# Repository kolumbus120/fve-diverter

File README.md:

# FVE diverter — solar surplus diverter for a Daikin heat-pump house (ESPHome + Home Assistant)

*[Slovenská verzia → README.sk.md](README.sk.md)*

An ESP32 (ESPHome) that sends **solar PV surplus into two electric heaters**: the domestic
hot water tank (3 kW element) and the underfloor heating water (~600 W element). Each heater is
driven by a TRIAC board controlled over I2C. Unlike a plain "keep the grid at 0 W" router, it
works with the **battery of a hybrid inverter (charging power and state of charge, SoC)** and with the **Daikin Altherma heat pump**. A set
of Home Assistant packages makes the slower decisions: when to turn the heat pump down because
the sun heats the house, when the heat pump must not heat the hot water because the sun will,
and a weekly heating plan with a custom Lovelace card.

It runs at home since 2026-11-15. The **PCB is designed and ordered but not built yet**
(see [PCB](#pcb--carrier-board) below).

*Main schematic: [SVG](docs/schematics/fve_schema_en.svg) · [PNG](docs/schematics/fve_schema_en.png) (Slovak original: [`fve_schema.svg`](docs/schematics/fve_schema.svg)).*

> Code comments and most of the docs in `docs/` are in **Slovak**. Entity names in Home Assistant
> are Slovak too (e.g. *TUV* = domestic hot water, *podlaha* = underfloor heating,
> *čerpadlo* = pump, *stykač* = contactor, *prebytok* = surplus, *okno FVE* = PV window).

## What it does

**ESP32 firmware** ([`esphome/fve-diverter.yaml`](esphome/fve-diverter.yaml)) — works without
Home Assistant too:

- **Measurement:** a Shelly 3EM-63 Gen3 at the grid connection is read directly by the ESP every
  2 s (local HTTP RPC). Battery power and SoC of the Solax hybrid inverter come from the Solax
  Cloud API through Home Assistant (about every 4 min).
- **How the surplus is split:** the floor first (0–600 W), then hot water and battery ¾ : ¼. The
  battery always keeps a 300 W reserve. At SoC ≥ 97 % everything goes to the hot water.
  - From the Shelly reading: when power is drawn from the grid, the heaters are cut quickly; when
    power flows out to the grid, they get more.
  - Each new Solax reading moves the heaters toward the target, taking into account what the
    heaters drew at the time of that reading.
- **Battery-aware (SoC):** unlike grid-only routers, it knows how much the battery is charging
  and its state of charge.
  - The battery gets its share first (300 W reserve, ¼ of the surplus above the floor element;
    the share is adjustable).
  - Once the battery counts as full (SoC ≥ 97 %, adjustable), the whole surplus goes to the hot
    water.
  - A weak Solcast forecast for tomorrow can raise the inverter's minimum SoC as a backup reserve
    (waits for a local Solax dongle).
- **Fail-safe:** no Shelly data for more than 15 s → heaters at 0 W. If Solax or HA is
  unavailable, an emergency Shelly-only mode heats only from the visible export and keeps about
  300 W of it.
- **TRIAC + contactors:** an isolation contactor in front of each TRIAC and a bypass contactor
  that takes over at ≥ 97 % power and opens again at ≤ 95 %. The TRIAC is held at 100 % before
  the bypass closes, so the contacts don't arc. At most one relay switches per 5 s cycle.
- **Phase-angle control** through DimmerLink: LINEAR curve plus a power → level table measured
  with the Shelly (error ≤ 1.5 %).
- **PV window from sunrise/sunset:** the window runs from sunrise + 2 h to sunset − 2 h. It is
  computed on the ESP with the ESPHome `sun:` component, and both offsets are adjustable.
  - Inside the window, the first surplus of at least 100 W lasting 5 min starts a **"sunny
    day"**. Only then do the contactors close, and they stay closed until the window ends.
  - On a cloudy day nothing switches at all.
  - The house sits in a valley: the history showed direct sun on the panels starts 2 h 40 min to
    3 h after sunrise and ends 2 h 15 min to 2 h 30 min before sunset.
- **Daikin integration via two 230 V AC opto inputs:**
  - Coil of the hydrobox **K3M** contactor (booster heater request) → the shared hot-water
    element runs at full power through the bypass, no matter what the PV is doing.
  - Floor pump request → floor circulation pump.
- **Limits:** hot water max 75 °C and floor water max 35 °C (adjustable, 2 °C hysteresis).
  - A failed DS18B20 (NaN) means no heating from PV.
  - TRIAC temperature is measured with an NTC.
- **Manual power** per heater, with a time limit (default 5 h) and a notification when it
  expires. After a reboot the ESP always returns to automatic mode.
- **Pumps:**
  - Floor pump: Auto (Daikin / PV heating) / always on / OFF.
  - Hot water circulation pump runs on tap use (flow meter), maintenance, during heating, and when
    the tank is hot while the sun shines.
  - Both pumps have a **hard OFF/ON mode for service** that overrides everything.
- **Fans:** 4-pin PWM cabinet fan with tachometer, following the TRIAC load; fans on the dimmer
  boards.
- **Energy counters (estimated):** hot water from PV, floor, and hot water via Daikin K3M.
  - The K3M energy is split into *from grid* / *from sun* using the Shelly: from grid = current
    grid import, at most the element power.
  - Daily and lifetime totals are kept on the ESP; weekly and monthly totals are utility meters
    in HA.
- **Diagnostics:** the reason for every regulation step, the measurement age, read-back from the
  DimmerLinks and more, all sent through HA to InfluxDB.

**Home Assistant** ([`home-assistant/`](home-assistant)):

- [`packages/fve_strategia.yaml`](home-assistant/packages/fve_strategia.yaml) — strategy:
  - **Daikin heating:** −10 °C water offset when it is a *sunny day* and the surplus is ≥ 700 W.
    At least 30 min between changes protects the compressor. On days without sun the heating plan
    runs untouched.
  - **Daikin hot water blocked so the sun can heat it:**
    - workdays 06:00–15:00;
    - days off: from the start of the PV window, released for the whole day if no sunny day
      starts within 60 min;
    - vacation: blocked all the time;
    - a manually started Daikin *performance* run always wins: it is never interrupted, and
      blocking is skipped for the rest of that day.
  - Tech M-9R zones +2 °C while the floor element runs at full power.
  - Hot water circulation during heating when somebody is at home.
  - Solcast forecast → Solax minimum SoC (waits for a local Solax dongle).
- [`packages/fve_energia.yaml`](home-assistant/packages/fve_energia.yaml) — weekly and monthly
  energy totals.
- **Heating plan:**
  - [`packages/daikin_plan_kurenia.yaml`](home-assistant/packages/daikin_plan_kurenia.yaml) — a
    weekly plan that switches between normal and setback by changing the water temperature offset
    on the Daikin.
  - It uses a week schedule plus a holiday schedule, Slovak public holidays (Workday + Holiday
    integrations), school holidays and vacation.
  - It produces one target-offset sensor; the sun-driven reduction from the strategy has priority.
  - Card [`www/plan-kurenia-card.js`](home-assistant/www/plan-kurenia-card.js) with dashboard
    [`dashboards/plan_kurenia.yaml`](home-assistant/dashboards/plan_kurenia.yaml): a weekly
    editor, today's plan, holiday list with on/off toggles, and a strip showing when the sun
    (PV strategy) and the low-tariff signal (HDO) were active.
- Dashboards: [`fve_diverter.yaml`](home-assistant/dashboards/fve_diverter.yaml) (operation),
  [`fve_diverter_test.yaml`](home-assistant/dashboards/fve_diverter_test.yaml) (service firmware).
- [`solax/`](home-assistant/solax) — Solax Cloud API v2 `command_line` sensor + script (until a
  local dongle is used).
- [`automations/`](home-assistant/automations) — notification when manual power expires.

**Grafana** ([`grafana/`](grafana)) — generator of a dashboard showing energy into the heaters
per day and power over time (InfluxDB v2 / Flux, data written by the HA InfluxDB integration).

## Hardware it was built and tested with

| Part | Used here | Notes |
|---|---|---|
| Controller | ESP32 DevKit 38-pin, ESPHome **2026.10.2** (Arduino framework) | pin map in [`esphome/README.md`](esphome/README.md) |
| TRIAC boards | 2× **RBDimmer** (rbdimmer.com) + 2× **DimmerLink** (I2C, 0x54 / 0x53) | modified DimmerLink component in [`esphome/components/dimmerlink`](esphome/components/dimmerlink) |
| Grid meter | **Shelly 3EM-63 Gen3** (`/rpc/EM.GetStatus`) | other Gen2+ Shelly EMs with the same RPC should work |
| Inverter | **Solax** hybrid with battery, Solax Cloud API v2 | without it: emergency Shelly-only mode |
| Heat pump | **Daikin Altherma 3** hydrobox EHBH08DA9W7 (K3M contactor = booster heater) | opto inputs on the K3M coil and the floor pump request |
| HA integrations | Home Assistant 2026.11, packages, `schedule`, Workday, Holiday; custom [`daikin_altherma`](https://github.com/tadasdanielius/daikin_altherma) (local LAN adapter) for the heating plan | Solcast, Tech controllers and ESPAltherma are optional |
| Other | DS18B20 ×3, 2-ch 230 V AC opto module, 2-ch relay modules, contactors, Hall flow meter, Mean Well MDR-20-5, 4-pin PWM fan | |

Adapt before use:
- the substitutions at the top of `fve-diverter.yaml`: `shelly_ip`, `latitude`, `longitude`;
- `secrets.yaml` (copy it from `secrets.yaml.example`);
- the element powers (calibrate with the Shelly);
- the DS18B20 addresses;
- the entity names in the HA packages (Daikin, Tech, Solax, notify).

## PCB — carrier board

[`pcb/`](pcb) — KiCad 9 project for a carrier board. The ESP32 and both DimmerLinks plug into
socket headers, and all wiring goes to locking JST-XH connectors. The board carries only 5 V and
3.3 V. The board is **generated by a Python script** (`gen_doska.py`), routed with Freerouting
(`route.py`) and gets GND stitching vias (`prechodky.py`). Gerbers are in `pcb/vyroba/`.

> ⚠️ **Rev B is ordered but not assembled or tested yet.** The header footprints of the ESP32 and
> the DimmerLink still need to be checked against real parts.
>
> ⚠️ **The resistors for the CUR-S current sense inputs (R9–R12) are not decided yet.** The
> output voltage of the RBDimmer CUR-S sensor is not specified by the manufacturer. The sensor
> chip has been identified as **CrossChip CC6920SO-50A** (5 V version, 40 mV/A, zero current =
> VCC/2, output 0.2–4.8 V, so it can go above 3.3 V). The first measurement gave **1.83 V** on CUR-S
> at zero current. That is not the expected 2.5 V, so the on-board trimmer probably acts as a
> divider. This is not confirmed yet. Leave **R9/R11 unpopulated** until it is:
> - CUR-S max ≤ 3.3 V → 0 Ω (or ~1 kΩ series) for R9/R11, no R10/R12;
> - CUR-S can exceed 3.3 V → a divider (proposed 10 kΩ / 18 kΩ, not verified yet).
>
> The firmware only displays CUR-S as a voltage; it is not used for regulation. Details:
> [`pcb/README.md`](pcb/README.md), [`docs/MERANIE_rbdimmer.md`](docs/MERANIE_rbdimmer.md).

## Repository layout

```
esphome/          ESPHome firmware (production + service/test version), DimmerLink component
home-assistant/   packages, dashboards, plan card (www), Solax cloud sensor, automation
grafana/          Grafana dashboard generator
pcb/              KiCad carrier board, generator scripts, gerbers, BOM (TME)
docs/             schematics (SVG/PNG + generators), dimmer calibration, measurements,
                  comparison with YaSolR, rbAmp power measurement plan
```

## Installation (short)

1. **Firmware:** `cd esphome`, `cp secrets.yaml.example secrets.yaml`, edit the substitutions,
   then `esphome run fve-diverter.yaml` (USB the first time, OTA after that). For bring-up, start
   with `fve-diverter-test.yaml`: nothing runs automatically there and everything is switched by
   hand from the service dashboard.
2. **HA packages:** set `homeassistant: packages: !include_dir_named packages`, copy
   `home-assistant/packages/*.yaml` to `/config/packages/`, restart HA, then run
   `script.fve_strategia_predvolene_hodnoty` once (default values of the helpers).
3. **Plan card:** copy `plan-kurenia-card.js` to `/config/www/`, add it as a resource
   `/local/plan-kurenia-card.js` (JavaScript module) and create a dashboard from
   `dashboards/plan_kurenia.yaml`.
4. **Solax cloud:** see [`home-assistant/solax/command_line.yaml`](home-assistant/solax/command_line.yaml).

## Status and known limitations

- The power going into the heaters is an **estimate** (dimmer level × calibrated element
  power), not a measurement. Measuring it with rbAmp modules is planned
  ([`docs/rbAmp_meranie_vykonu.md`](docs/rbAmp_meranie_vykonu.md)).
- Until a local Solax dongle is installed, battery data come from the cloud and are 1–5 min old.
  When it gets cloudy, the inverter can cover the heaters from the battery for a short while.
  The 300 W battery reserve limits this.
- Phase-angle control only (no cycle stealing); an EMI filter is used on the hot-water branch.

## Safety

This controls **230/400 V loads and contactors**. Build it only if you are qualified to do
mains wiring. It must have independent protection that does not depend on the ESP: an RCD, a
fuse or breaker per heater, a mechanical thermostat or thermal cut-out on every heater, and an
isolation contactor in front of each TRIAC (a failed TRIAC usually stays shorted). A "hard
OFF" in the software is not an isolation: always switch the breaker off before touching the
wiring.

## Credits

- **[RBDimmer / RobotDyn](https://rbdimmer.com)** — RBDimmer TRIAC boards and **DimmerLink**.
  The ESPHome component in `esphome/components/dimmerlink` is a modified copy of
  [robotdyn-dimmer/DimmerLink](https://github.com/robotdyn-dimmer/DimmerLink) (© 2024 RBDimmer,
  MIT); the change (register read-back fix) is described in
  [`NOTICE.md`](esphome/components/dimmerlink/NOTICE.md).
- **[YaSolR](https://github.com/mathieucarbou/YaSolR)** by Mathieu Carbou — a well-known
  open-source solar router. It was used for comparison and ideas (e.g. the time limit for manual
  mode, the PI regulator plans); no code was copied. See
  [`docs/porovnanie_yasolr_fve_diverter.md`](docs/porovnanie_yasolr_fve_diverter.md).
- **[ESPHome](https://esphome.io)** and **[Home Assistant](https://www.home-assistant.io)**.
- **[daikin_altherma](https://github.com/tadasdanielius/daikin_altherma)** by Tadas Danielius —
  local Daikin integration used by the heating plan.
- **[ESPAltherma](https://github.com/raomin/ESPAltherma)** by raomin — Daikin data incl. the
  low-tariff (HDO) signal shown on the plan card (optional).
- **[Solcast PV Forecast](https://github.com/BJReplay/ha-solcast-solar)** integration (optional),
  **Shelly**, **Solax Cloud API**.
- **[KiCad](https://www.kicad.org)** and **[Freerouting](https://github.com/freerouting/freerouting)**
  for the PCB.
- Designed and built by **kolumbus120**, with **[Claude Code](https://claude.com/claude-code)**
  (Anthropic) as an AI pair programmer for firmware, HA configuration, PCB scripts and docs.

## License

**GPL-3.0** — see [`LICENSE`](LICENSE). This applies to the firmware, Home Assistant
configuration, scripts, documentation and the PCB design. Exception:
`esphome/components/dimmerlink/` stays under its original **MIT** license.

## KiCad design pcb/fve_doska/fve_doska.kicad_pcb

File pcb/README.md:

# Základná doska FVE divertera (ESP32 + 2× DimmerLink)

> ⚠️ **Not tested yet / zatiaľ neoverené (2026-11-17):** doska rev B je objednaná, ale ešte nie je
> osadená ani oživená. Rozmery líšt ESP32 a DimmerLinku treba overiť na reálnych kusoch.
>
> ⚠️ **Rezistory pre CUR-S (R9–R12) ešte nie sú určené.** Napätie výstupu prúdového snímača
> CUR-S na doskách rbdimmer výrobca neuvádza a zatiaľ sme ho nezmerali. Kým nebude zmerané,
> **R9/R11 neosadzuj** (CUR-S je tak od ESP32 odpojený; firmvér ho aj tak len zobrazuje ako napätie, na reguláciu sa nepoužíva).
> Snímač na 3,3 V → R9/R11 = 0 Ω, R10/R12 neosadiť; na 5 V → delič (návrh R9/R11 10 kΩ +
> R10/R12 18 kΩ, ešte neoverený). Postup merania: [`../docs/MERANIE_rbdimmer.md`](../docs/MERANIE_rbdimmer.md).

KiCad 9 projekt: `fve_doska/fve_doska.kicad_pro`. Generuje ho `gen_doska.py`. Pri zmene
rozmerov alebo zapojenia upraviť generátor a spustiť znova. Ručné úpravy v KiCade sa
pri ďalšom generovaní prepíšu.

**Stav (rev B): OBJEDNANÁ 2026-11-16** — Gerbery `vyroba/fve_doska_gerber.zip` z commitu
`96e6954` (posun konektorov + prepojovacie priechody GND). Freerouting 2.5, 0 nespojených, DRC
bez chýb spojov aj medzier — zostali len kozmetické upozornenia potlače a 4× „starved thermal“
pri GND pinoch, ktoré sú pripojené aj trasou. Napájanie a GND 1 mm (pri pinoch min 0,4),
signály 0,4 mm, všetky medzery min 0,4 mm, GND vyliaty na oboch vrstvách + 114 prepojovacích
priechodov (prekryté maskou). Na spodnej potlači „rev B 2026-11“.

**rev B oproti rev A:** J15 I2C zmenený z XH-4 na **XH-5 s 5 V** + nový rovnaký **J18** pod ním
(2× rbAmp UI1 — TUV a podlaha, viď `../docs/rbAmp_meranie_vykonu.md`). Inak bez zmeny.
rev A (commit `5b418e1`) mal user prvú objednanú — ak by prišla rev A, J15 je len XH-4 bez 5 V
(5 V pre rbAmp potom priamo zo zdroja Mean Well).
Poradie pinov DimmerLinku 2CH overil user fyzicky (2026-11-15) — sedí.

⚠️ `gen_doska.py` dosku vygeneruje znova BEZ trás → po každej zmene spustiť aj `route.py`.

Náhľad: `fve_doska/nahlad_doska.png` · schéma: `fve_doska/fve_doska_schema.pdf` · nákup: [`NAKUP_TME.md`](NAKUP_TME.md)

## Zásady

- Na doske je **len 5 V a 3,3 V**. 230 V ostáva na relé moduloch, opto module a doskách
  rbdimmer.
- ESP32 a DimmerLinky sú zasunuté v dutinkových lištách, dajú sa vymeniť.
- Všetko s tenkými káblami (snímače, prietok, opto, relé moduly, rbdimmery) je na zacvakávacích
  **JST-XH so zámkom** (rozteč 2,5 mm). Krimpuje sa bežnými kliešťami pre JST-XH (XH-2…6). Na strane
  modulov (relé, opto, rbdimmer s kolíkmi 2,54 mm) je kábel ukončený DuPont puzdrom zo sady.
  Rbdimmer má 2 konektory XH-4 (riadenie a snímače), lebo sada má XH najviac 6-pin.
- Len napájanie 5 V je na bezskrutkovej svorke **WAGO 2601-3102** (push-in, vodič zhora,
  do 1,5 mm², každý pól 2 nožičky kvôli pevnosti).
- Rezistory sú priletované na doske. GND je vyliaty na oboch vrstvách. Pod anténou ESP32
  nie je meď.

## Svorky (poradie pinov = poradie na doske, popis na potlači)

| Svorka | Piny | Kam |
|---|---|---|
| J1 NAPÁJANIE 5V (WAGO) | 5V GND | Mean Well MDR-20-5 |
| J2 B1 BOJLER (XH-3) | 3V3 GND DQ (G21, R1) | DS18B20 |
| J3 B2 VRATNÁ (XH-3) | 3V3 GND DQ (G5, R7 — alebo G21 cez JP5) | DS18B20 |
| J4 B3 PODLAHA (XH-3) | 3V3 GND DQ (G13, R8 — alebo G21 cez JP6) | DS18B20 |
| J5 PRIETOK TUV (XH-3) | 3V3 GND SIG (G4, R6) | Hall prietokomer |
| J6 OPTO DAIKIN + 5V (XH-6) | 5V GND K3M (G14) ČERP (G27) GND 3V3 | AC opto modul (VCC = 3V3!) + napájanie ESPAltherma 5 V |
| J7 RELÉ TUV (XH-5) | GND IN1 (G17 stykač) IN2 (G16 bypass) 3V3 5V(JD-VCC) | 2-kan. relé |
| J8 RELÉ PODLAHA (XH-5) | GND IN1 (G19) IN2 (G18) 3V3 5V | 2-kan. relé |
| J9 RELÉ ČERPADLÁ (XH-5) | GND TUV (G26) POD (G25) 3V3 5V | 2-kan. relé |
| J10 RBDIMMER TUV riadenie (JST-XH 4) | 3V3 GND ZC DIM | doska D1 (ZC/DIM z DimmerLinku TUV, I2C 0x54) |
| J11 RBDIMMER TUV snímače (JST-XH 4) | TEMP CUR FAN 5V | doska D1 |
| J13 RBDIMMER POD riadenie (JST-XH 4) | 3V3 GND ZC DIM | doska D2 (ZC/DIM z DimmerLinku podlaha, I2C 0x53) |
| J14 RBDIMMER POD snímače (JST-XH 4) | TEMP CUR FAN 5V | doska D2 |
| J12 FAN SKRINE (XH-4) | GND 5V TACHO (G22) PWM (G23) | ventilátor skrine (pôvodný konektor fanu nahradený JST-XH) |
| J15 I2C (1) (XH-5) | 3V3 GND SDA (G2) SCL (G15) 5V | rbAmp TUV (GND SDA SCL 5V, 3V3 nezapájať) alebo SHT/BME/DS2482 (3V3) |
| J18 I2C (2) (XH-5) | 3V3 GND SDA (G2) SCL (G15) 5V | rbAmp podlaha — rovnaké ako J15, pod ním (rev B, 2026-11-16) |
| J16 ONEWIRE (1) (XH-3) | 3V3 GND DQ — cez JP7: 1-2 G5 (R7), 2-3 G21 | ďalšie DS18B20 |
| J17 ONEWIRE (2) (XH-3) | 3V3 GND DQ — cez JP8: 1-2 G13 (R8), 2-3 G21 | ďalšie DS18B20 |

**Prepojky OneWire JP5–JP8:** podrobný návod je nižšie v sekcii „Prepojky OneWire JP5–JP8 — návod“.

**TEMP** (NTC 10k proti GND, overené) ide priamo na ESP: TUV G36, podlaha G34, pull-up R4/R5 10 kΩ.
**CUR-S** ide na ESP cez R9/R11 (G39/G35). **R9/R11 osadiť až po zmeraní** napätia snímača
([`../docs/MERANIE_rbdimmer.md`](../docs/MERANIE_rbdimmer.md)): snímač na 3,3 V → R9/R11 = 0 Ω, R10/R12 neosadiť; na 5 V → delič.
Kým R9/R11 chýba, CUR-S je od ESP odpojený.

## Prepojky OneWire JP5–JP8 — návod

*(Napísané 2026-11-16, aby sa to dalo pochopiť aj o pár rokov.)*

### Prečo to tam je

Teplomery DS18B20 komunikujú cez OneWire: jeden dátový vodič (DQ, žltý), na ktorom môže byť
aj viac snímačov naraz (tzv. zbernica). **Lacné klony DS18B20, ktoré máme (2026-11-14), po dvoch
na jednej zbernici nefungujú** (ESP číta samé nuly). Preto má každý z nich vlastný pin ESP32:

| Pin ESP32 | Pull-up (4,7 kΩ na 3,3 V) | Názov vo firmvéri (`one_wire` id) | Pevne zapojený |
|---|---|---|---|
| **G21** | R1 | `ow_bus` | **B1 BOJLER (J2) — vždy, bez prepojky** |
| **G5** | R7 | `ow_vratna` | nie, cez JP5 alebo JP7 |
| **G13** | R8 | `ow_podlaha` | nie, cez JP6 alebo JP8 |

Prepojky rozhodujú, ktorý konektor dostane ktorý pin. Keď raz kúpiš originálne (alebo
overené) snímače, ktoré zvládnu spoločnú zbernicu, dajú sa B2 a B3 presunúť na G21 a uvoľnené
piny G5 / G13 použiť pre nové konektory ONEWIRE (1) J16 a ONEWIRE (2) J17.

### Ako vyzerá prepojka

Každá JP je 3-pinová lišta s jedným jumperom. **Prostredný pin (2) = DQ konektora.** Jumper ho
spojí buď s pinom 1 (vlastný pin), alebo s pinom 3 (spoločná zbernica G21):

```
          pin 1 ── G5 / G13  (vlastný pin, vlastný pull-up R7 / R8)
JP  ──┤   pin 2 ── DQ konektora (B2, B3, J16 alebo J17)
          pin 3 ── G21       (zbernica bojlera, pull-up R1)

jumper na 1-2 → konektor je na vlastnom pine
jumper na 2-3 → konektor je na spoločnej zbernici G21 (spolu s bojlerom B1)
bez jumpera   → konektor je odpojený (nič sa nepokazí)
```

| Prepojka | Pre konektor | 1-2 | 2-3 | Kde na doske | Pin 1 (štvorcová ploška) |
|---|---|---|---|---|---|
| **JP5** | B2 VRATNÁ (J3) | G5 | G21 | vľavo dole, nad J3, vedľa R7 | **hore** |
| **JP6** | B3 PODLAHA (J4) | G13 | G21 | vľavo dole, nad J4, vedľa R8 | **hore** |
| **JP7** | ONEWIRE (1) (J16) | G5 | G21 | vpravo v strede, pod J16 | **vľavo** |
| **JP8** | ONEWIRE (2) (J17) | G13 | G21 | vpravo v strede, pod J17 | **vľavo** |

Popis „1-2 G5 / 2-3 G21“ (resp. G13) je pri každej prepojke na potlači.

### Pravidlá

1. **G5 smie dostať len jeden konektor:** buď JP5 (B2), alebo JP7 (J16) v polohe 1-2, nie obe.
   **G13 rovnako:** buď JP6 (B3), alebo JP8 (J17). Na doske je to pripomenuté nápisom
   „JP5+JP7 / JP6+JP8 nie naraz 1-2!“. Elektricky sa nič nepokazí, ale dva snímače na jednom
   pine = zbernica a klony na zbernici nefungujú.
2. **Na G21 (poloha 2-3) dávaj len snímače, ktoré na zbernici preukázateľne fungujú.** Na G21
   je vždy aj bojler B1 — chybný alebo nevhodný snímač môže zablokovať celú zbernicu a bojler
   potom ukazuje nezmysel / „unknown“. Regulácia TUV pri neplatnej teplote bojlera nehreje.
3. **Na vlastnom pine (1-2) môže byť aj viac snímačov** (napr. na J16 rozdvojený kábel), ale
   platí to isté: zbernicu zvládnu len dobré snímače. Jeden klon = vždy sám na pine.
4. **Po každej zmene prepojok treba upraviť aj firmvér** (nižšie) — ESP nevie, kde je jumper.
5. Prepojky prestavovať **bez napätia** (vypnúť 5 V zdroj).
6. G5 je „strapping“ pin ESP32 (pri štarte má byť v log. 1, R7 to zaručí). Ak by ESP po
   pripojení snímača na G5 nenaštartovalo, vytiahni jumper JP5 / JP7 a skús znova.

### Platné nastavenia

| Situácia | JP5 | JP6 | JP7 | JP8 | Firmvér |
|---|---|---|---|---|---|
| **A — teraz (stav 2026-11): klony, každý sám** | 1-2 | 1-2 | bez jumpera alebo 2-3 * | bez jumpera alebo 2-3 * | `ow_b2: ow_vratna`, `ow_b3: ow_podlaha` (tak je to teraz) |
| **B — B2 a B3 originálne na G21, J16/J17 na vlastných pinoch** | 2-3 | 2-3 | 1-2 | 1-2 | `ow_b2: ow_bus`, `ow_b3: ow_bus`; snímač J16 na `ow_vratna`, J17 na `ow_podlaha` |
| **C — iba B2 na G21, B3 ostáva sám** | 2-3 | 1-2 | 1-2 | 2-3 alebo bez | `ow_b2: ow_bus`; snímač J16 na `ow_vratna`, J17 (ak je) na `ow_bus` |
| **D — iba B3 na G21, B2 ostáva sám** | 1-2 | 2-3 | 2-3 alebo bez | 1-2 | `ow_b3: ow_bus`; snímač J17 na `ow_podlaha`, J16 (ak je) na `ow_bus` |

\* Kým na J16/J17 nič nie je, na polohe nezáleží. Odporúčam jumper odložiť nasadený len na
jeden pin (aby sa nestratil) — konektor je potom odpojený.

**Zakázané:** JP5 a JP7 obe v 1-2 (dva konektory na G5), JP6 a JP8 obe v 1-2 (dva na G13).

### Firmvér (`../esp32-fve-diverter/fve-diverter.yaml`)

Tri zbernice sú vo firmvéri definované vždy rovnako (sekcia `one_wire:`), menia sa len
priradenia snímačov. Pozor: názvy `ow_vratna` / `ow_podlaha` znamenajú **pin G5 / G13**, nie
konkrétny snímač — keď sa B2 presunie na G21, `ow_vratna` (G5) potom slúži pre J16.

- **B2 a B3** sa prepínajú substitúciami na začiatku súboru:
  ```yaml
  substitutions:
    ow_b2: ow_vratna    # JP5 1-2 (G5);  pri JP5 2-3 → ow_bus
    ow_b3: ow_podlaha   # JP6 1-2 (G13); pri JP6 2-3 → ow_bus
  ```
- **J16 / J17** (zatiaľ vo firmvéri nie sú) — doplniť snímač do sekcie `sensor:`:
  ```yaml
    - platform: dallas_temp
      one_wire_id: ow_vratna        # J16: JP7 1-2 → ow_vratna (G5), JP7 2-3 → ow_bus (G21)
      address: 0x...                # adresu zistiť z logov (nižšie)
      name: "Teplota ..."
      update_interval: 30s
  ```
  (J17: JP8 1-2 → `ow_podlaha` (G13), JP8 2-3 → `ow_bus`.)
- **Vždy s adresou** (`address:`). Bez nej ESPHome berie snímače podľa poradia a po reštarte by
  si mohli vymeniť miesta (napr. TUV by ukazovala podlahu).
- **Zistenie adresy nového snímača:** pripojiť ho samotný, nahrať firmvér, v logoch ESPHome
  hľadať „Found sensors: 0x…“ (postup je aj v komentári nad `one_wire:` v YAML-e). Adresu zapísať
  do YAML-u a kábel snímača oštítkovať.

### Postup pri zmene (krok za krokom)

1. Vypnúť napájanie 5 V.
2. Prestaviť prepojky podľa tabuľky „Platné nastavenia“ (skontrolovať pravidlo č. 1).
3. Pripojiť snímače.
4. Upraviť `fve-diverter.yaml` (substitúcie / nové snímače s adresami), nahrať (OTA).
5. Zapnúť, v logoch skontrolovať „Found sensors“ na každej zbernici a v HA všetky teploty —
   **hlavne bojler B1**, od ktorého závisí regulácia TUV.

### Keď niečo nejde

- **Bojler B1 po pridaní snímača na G21 ukazuje nezmysel / „unknown“:** nový snímač zbernicu
  nezvláda → daj ho na vlastný pin (prepojka 1-2), alebo vytiahni jeho jumper.
- **Snímač nie je vidieť vôbec:** je jumper nasadený? Sedí `one_wire_id` vo firmvéri s polohou
  jumpera? Sedí adresa?
- **Teplota 85 °C:** typická hodnota DS18B20 po zapnutí / pri zlom napájaní — skontrolovať
  kábel (3V3, GND).

## Zoznam súčiastok

| Ks | Súčiastka | Pozn. |
|---|---|---|
| 2 | dutinková lišta 1x19, 2,54 mm | pätica ESP32 (U1) |
| 2 + 2 | dutinková lišta 1x4 + 1x5, 2,54 mm | pätice DimmerLinkov (U2, U3), overiť |
| 1 | WAGO 2601-3102 | J1 |
| 6 | JST-XH 3-pin (XH-3A na dosku + XH-3Y puzdro) | J2–J5, J16, J17 (zo sady) |
| 5 | JST-XH 4-pin (XH-4A + XH-4Y) | J10–J14 (zo sady) |
| 5 | JST-XH 5-pin (XH-5A + XH-5Y) | J7–J9, J15, J18 (zo sady) |
| 1 | JST-XH 6-pin (XH-6A + XH-6Y) | J6 (zo sady) |
| 4 | kolíková lišta 1x3 + jumper | JP5–JP8 (OneWire) |
| — | kontakty JST-XH + DuPont puzdrá 1x3/1x4/1x5/1x8 na strane modulov | zo sady |
| 6 | rezistor 4,7 kΩ 0,25 W | R1–R3, R6–R8 |
| 2 | rezistor 10 kΩ 0,25 W | R4, R5 |
| 2 | 0 Ω alebo delič — až po zmeraní CUR-S | R9, R11 (R10, R12 len pri 5 V) |
| 3 | kondenzátor 100 nF, keramický, rozteč 5 mm | C2–C4 |
| 1 | elektrolyt 470 µF / 10 V, Ø8 mm | C1 |
| 1 | elektrolyt 47 µF / 10 V, Ø5 mm | C5 |

C3, C4 (100 nF pri DimmerLinkoch) odporúča výrobca DimmerLinku na odfiltrovanie rušenia
na 3,3 V. Bez nich to funguje, na doske sú ako poistka.

## Otvorené

- [x] ESP32: rozteč radov ~25,5 mm (user) → 25,4 mm (1").
- [x] DimmerLink: vzdialenosť líšt ~12,5 mm (user) → 12,7 mm.
- [x] DimmerLink 2CH: vstup 1x4 VCC GND SDA SCL, výstup 1x5 VCC GND ZC DIM0 DIM1 — overené.
- [x] Doska 130 × 80 mm na šírku (kvôli cene), relé v jednom rade vedľa seba, 6× M3 pre dištančné stĺpiky (4 rohy, medzi ESP a relé, stred dolnej strany).
      ESP32 naležato vľavo, anténa k ľavému okraju (pod ňou bez medi).
- [x] Natrasované (`route.py` = Freerouting 2.5 + OpenJDK 25), DRC OK.
- [x] Gerber + vŕtanie: `vyroba/fve_doska_gerber.zip` (rev A 2026-11-15, **rev B 2026-11-16**).
- [x] rev B: J15 + J18 I2C XH-5 s 5 V (rbAmp).
- [x] rev B (2026-11-16, úprava): OneWire J16 +2 mm a J17 +1 mm doprava, I2C J15/J18 a relé J7/J8/J9 o 1 mm dole; znova natrasované.
- [x] rev B: 114 prepojovacích priechodov GND (vrch ↔ spodok), `prechodky.py`.
- [x] **rev B objednaná 2026-11-16** (Gerbery z commitu `96e6954`).
- [ ] Po príchode: osadiť, oživiť, overiť rozmery líšt ESP32 / DimmerLink.

## Generovanie

```
python3 gen_doska.py                       # schéma + doska (rozmiestnenie)
python3 route.py <freerouting-2.5.0.jar>   # autorouter (Java 25: /usr/lib/jvm/java-25-openjdk-amd64)
#   na konci spustí prechodky.py: vyliatie GND + prepojovacie priechody GND (mriežka 5 mm, 0,8/0,4 mm)
#   dá sa spustiť aj samostatne na natrasovanej doske: python3 prechodky.py
#   route.py: trasuje s medzerou 0,42 mm (rezerva na rozšírenie zúžení), uloží s pravidlom 0,4 mm;
#   zúžené trasy rozširuje textovo a GND vylieva v novom procese (KiCad 9.0.2: po importe SES
#   je väzba pcbnew v Pythone pokazená — GetTracks/LoadBoard vracajú SwigPyObject)
kicad-cli sch erc fve_doska/fve_doska.kicad_sch
kicad-cli pcb drc fve_doska/fve_doska.kicad_pcb
```

## Objednanie dosky

Súbor na nahratie: **`vyroba/fve_doska_gerber.zip`** (Gerber + vŕtanie, KiCad 9).
Pri zmene dosky: `gen_doska.py` → `route.py` → znova exportovať (príkazy nižšie).

Parametre (napr. JLCPCB / PCBWay):

| Parameter | Hodnota |
|---|---|
| Vrstvy | 2 |
| Rozmer | 130 × 80 mm |
| Hrúbka | 1,6 mm |
| Meď | 1 oz (35 µm) |
| Povrch | HASL (bezolovnatý podľa chuti) |
| Min. trasa / medzera | 0,4 / 0,4 mm (bežné, bez príplatku) |
| Min. vŕtanie | 0,4 mm (via) |
| Počet | 5 ks (minimum); user plánuje 10 ks (pre známych, +~5 €) |
| Osadenie | nie — súčiastky s vývodmi osádza user |

```
kicad-cli pcb export gerbers --layers F.Cu,B.Cu,F.Mask,B.Mask,F.SilkS,B.SilkS,Edge.Cuts \
  --subtract-soldermask --no-x2 -o vyroba/gerber/ fve_doska/fve_doska.kicad_pcb
kicad-cli pcb export drill --format excellon --excellon-separate-th -o vyroba/gerber/ fve_doska/fve_doska.kicad_pcb
```

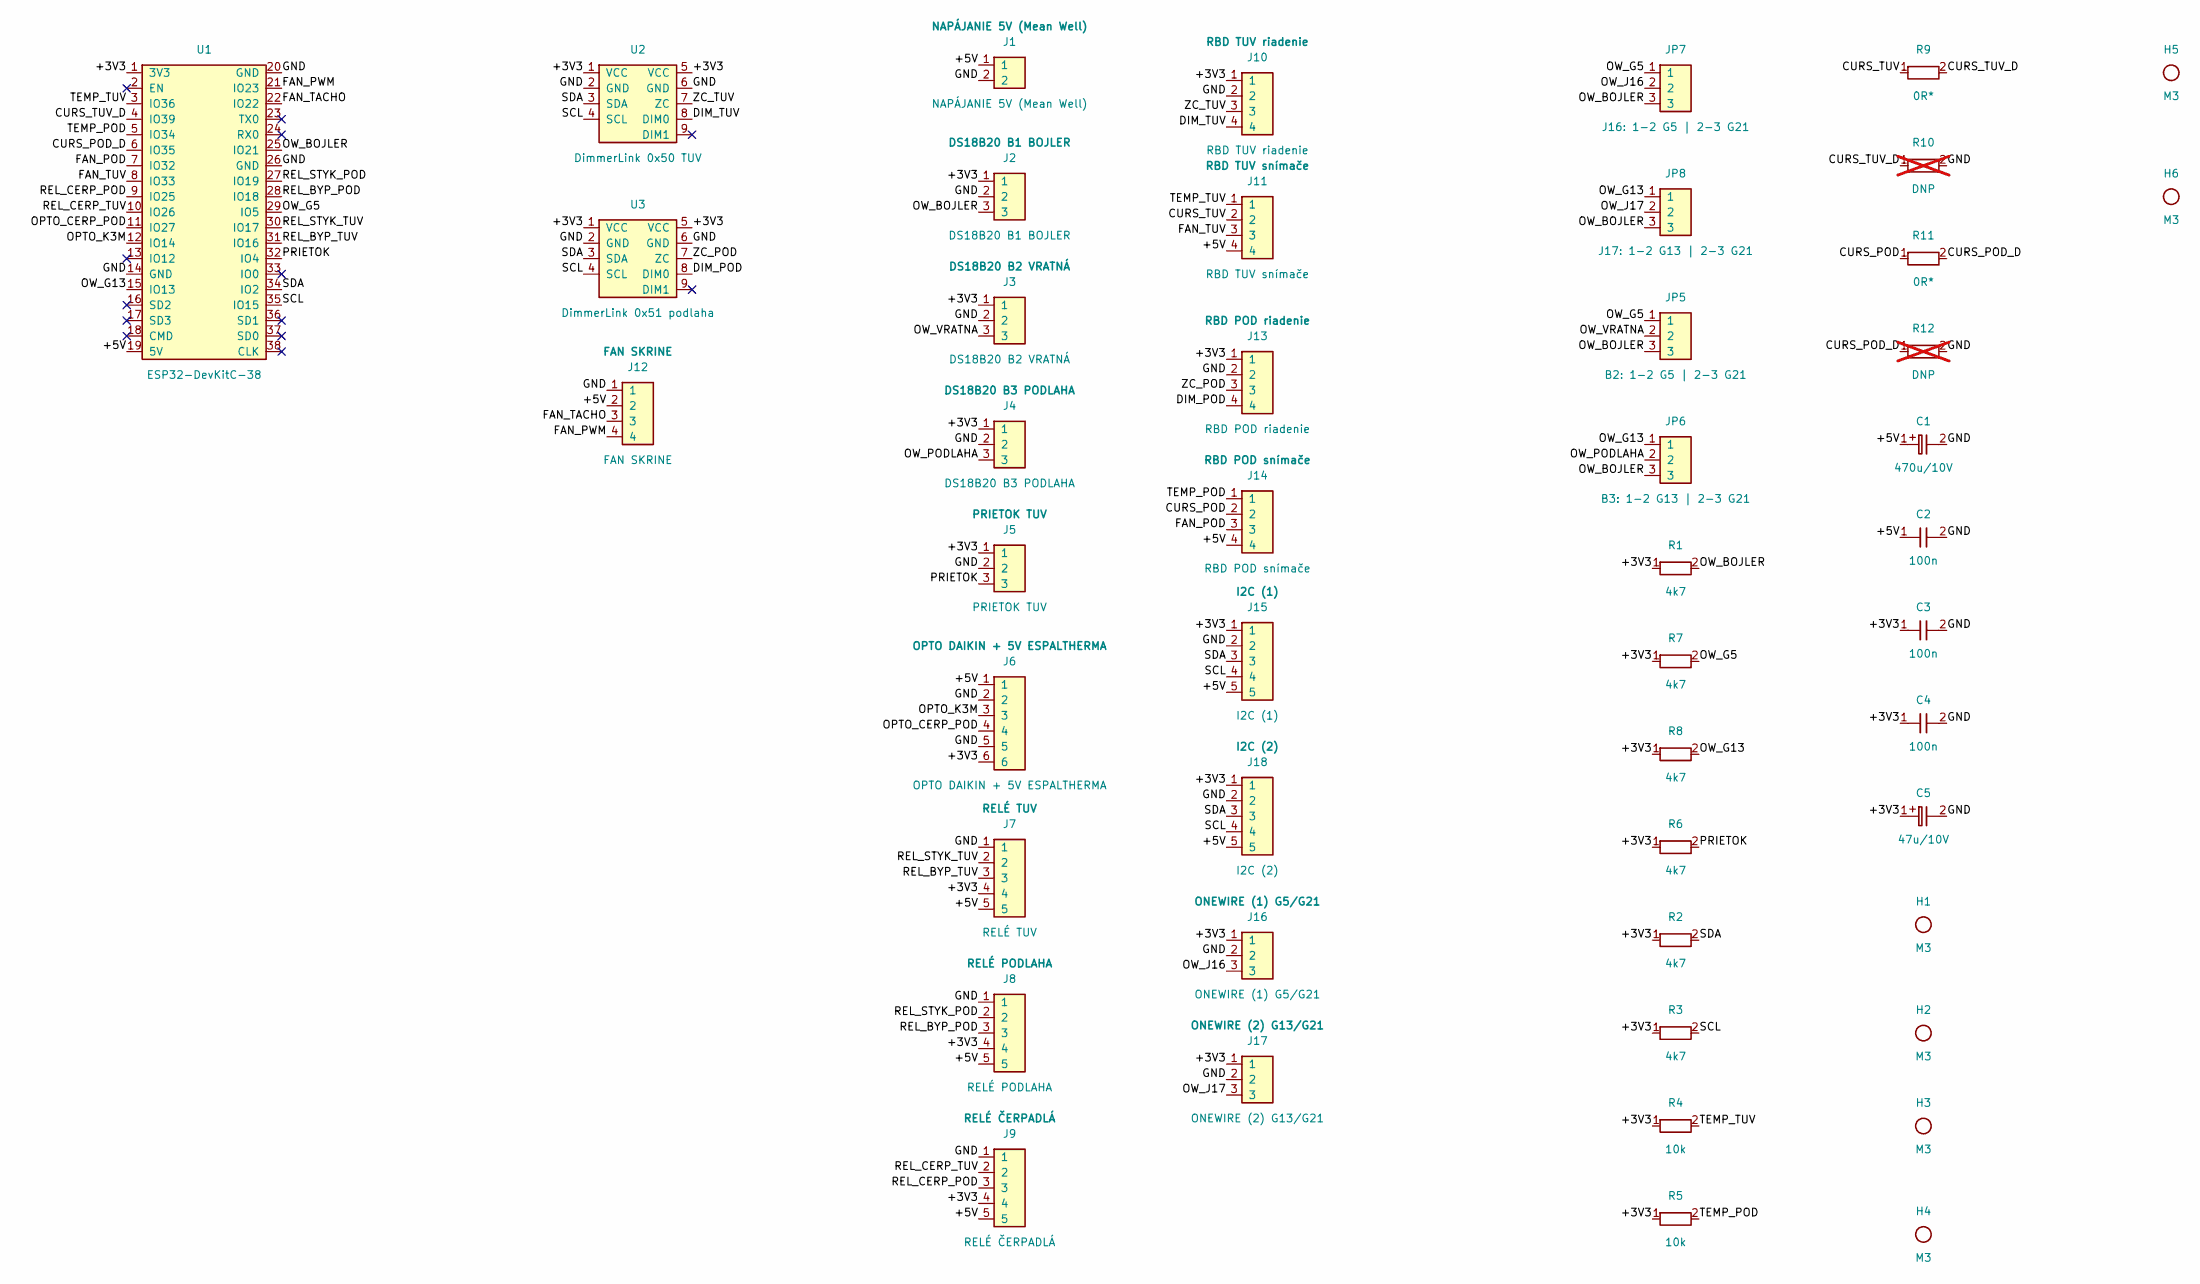
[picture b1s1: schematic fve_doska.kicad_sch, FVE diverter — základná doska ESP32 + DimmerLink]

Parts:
C1: 470u/10V; CP_Radial_D8.0mm_P3.50mm
C2, C3, C4: 100n; C_Disc_D5.0mm_W2.5mm_P5.00mm
C5: 47u/10V; CP_Radial_D5.0mm_P2.00mm
H1, H2, H3, H4, H5, H6: M3; MountingHole_3.2mm_M3
J1: NAPÁJANIE 5V (Mean Well); TerminalBlock_WAGO_2601-3102_1x02_P3.50mm_Vertical
J2: DS18B20 B1 BOJLER; JST_XH_B3B-XH-A_1x03_P2.50mm_Vertical
J3: DS18B20 B2 VRATNÁ; JST_XH_B3B-XH-A_1x03_P2.50mm_Vertical
J4: DS18B20 B3 PODLAHA; JST_XH_B3B-XH-A_1x03_P2.50mm_Vertical
J5: PRIETOK TUV; JST_XH_B3B-XH-A_1x03_P2.50mm_Vertical
J6: OPTO DAIKIN + 5V ESPALTHERMA; JST_XH_B6B-XH-A_1x06_P2.50mm_Vertical
J7: RELÉ TUV; JST_XH_B5B-XH-A_1x05_P2.50mm_Vertical
J8: RELÉ PODLAHA; JST_XH_B5B-XH-A_1x05_P2.50mm_Vertical
J9: RELÉ ČERPADLÁ; JST_XH_B5B-XH-A_1x05_P2.50mm_Vertical
J10: RBD TUV riadenie; JST_XH_B4B-XH-A_1x04_P2.50mm_Vertical
J11: RBD TUV snímače; JST_XH_B4B-XH-A_1x04_P2.50mm_Vertical
J12: FAN SKRINE; JST_XH_B4B-XH-A_1x04_P2.50mm_Vertical
J13: RBD POD riadenie; JST_XH_B4B-XH-A_1x04_P2.50mm_Vertical
J14: RBD POD snímače; JST_XH_B4B-XH-A_1x04_P2.50mm_Vertical
J15: I2C (1); JST_XH_B5B-XH-A_1x05_P2.50mm_Vertical
J16: ONEWIRE (1) G5/G21; JST_XH_B3B-XH-A_1x03_P2.50mm_Vertical
J17: ONEWIRE (2) G13/G21; JST_XH_B3B-XH-A_1x03_P2.50mm_Vertical
J18: I2C (2); JST_XH_B5B-XH-A_1x05_P2.50mm_Vertical
JP5: B2: 1-2 G5 | 2-3 G21; PinHeader_1x03_P2.54mm_Vertical
JP6: B3: 1-2 G13 | 2-3 G21; PinHeader_1x03_P2.54mm_Vertical
JP7: J16: 1-2 G5 | 2-3 G21; PinHeader_1x03_P2.54mm_Vertical
JP8: J17: 1-2 G13 | 2-3 G21; PinHeader_1x03_P2.54mm_Vertical
R1, R2, R3, R6, R7, R8: 4k7; R_Axial_DIN0207_L6.3mm_D2.5mm_P10.16mm_Horizontal
R4, R5: 10k; R_Axial_DIN0207_L6.3mm_D2.5mm_P10.16mm_Horizontal
R9, R11: 0R*; R_Axial_DIN0207_L6.3mm_D2.5mm_P10.16mm_Horizontal
R10, R12: DNP; R_Axial_DIN0207_L6.3mm_D2.5mm_P10.16mm_Horizontal; not fitted
U1: ESP32-DevKitC-38; ESP32_DevKitC_38_Socket
U2: DimmerLink 0x50 TUV; DimmerLink_2CH_Socket
U3: DimmerLink 0x51 podlaha; DimmerLink_2CH_Socket

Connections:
+3V3: C3.1, C4.1, C5.1, J2.1, J3.1, J4.1, J5.1, J6.6, J7.4, J8.4, J9.4, J10.1, J13.1, J15.1, J16.1, J17.1, J18.1, R1.1, R2.1, R3.1, R4.1, R5.1, R6.1, R7.1, R8.1, U1.1 (3V3), U2.1 (VCC), U2.5 (VCC), U3.1 (VCC), U3.5 (VCC)
+5V: C1.1, C2.1, J1.1, J6.1, J7.5, J8.5, J9.5, J11.4, J12.2, J14.4, J15.5, J18.5, U1.19 (5V)
CURS_POD: J14.2, R11.1
CURS_POD_D: R11.2, R12.1, U1.6 (IO35)
CURS_TUV: J11.2, R9.1
CURS_TUV_D: R9.2, R10.1, U1.4 (IO39)
DIM_POD: J13.4, U3.8 (DIM0)
DIM_TUV: J10.4, U2.8 (DIM0)
FAN_POD: J14.3, U1.7 (IO32)
FAN_PWM: J12.4, U1.21 (IO23)
FAN_TACHO: J12.3, U1.22 (IO22)
FAN_TUV: J11.3, U1.8 (IO33)
GND: C1.2, C2.2, C3.2, C4.2, C5.2, J1.2, J2.2, J3.2, J4.2, J5.2, J6.2, J6.5, J7.1, J8.1, J9.1, J10.2, J12.1, J13.2, J15.2, J16.2, J17.2, J18.2, R10.2, R12.2, U1.14 (GND), U1.20 (GND), U1.26 (GND), U2.2 (GND), U2.6 (GND), U3.2 (GND), U3.6 (GND)
OPTO_CERP_POD: J6.4, U1.11 (IO27)
OPTO_K3M: J6.3, U1.12 (IO14)
OW_BOJLER: J2.3, JP5.3, JP6.3, JP7.3, JP8.3, R1.2, U1.25 (IO21)
OW_G5: JP5.1, JP7.1, R7.2, U1.29 (IO5)
OW_G13: JP6.1, JP8.1, R8.2, U1.15 (IO13)
OW_J16: J16.3, JP7.2
OW_J17: J17.3, JP8.2
OW_PODLAHA: J4.3, JP6.2
OW_VRATNA: J3.3, JP5.2
PRIETOK: J5.3, R6.2, U1.32 (IO4)
REL_BYP_POD: J8.3, U1.28 (IO18)
REL_BYP_TUV: J7.3, U1.31 (IO16)
REL_CERP_POD: J9.3, U1.9 (IO25)
REL_CERP_TUV: J9.2, U1.10 (IO26)
REL_STYK_POD: J8.2, U1.27 (IO19)
REL_STYK_TUV: J7.2, U1.30 (IO17)
SCL: J15.4, J18.4, R3.2, U1.35 (IO15), U2.4 (SCL), U3.4 (SCL)
SDA: J15.3, J18.3, R2.2, U1.34 (IO2), U2.3 (SDA), U3.3 (SDA)
TEMP_POD: J14.1, R5.2, U1.5 (IO34)
TEMP_TUV: J11.1, R4.2, U1.3 (IO36)
ZC_POD: J13.3, U3.7 (ZC)
ZC_TUV: J10.3, U2.7 (ZC)

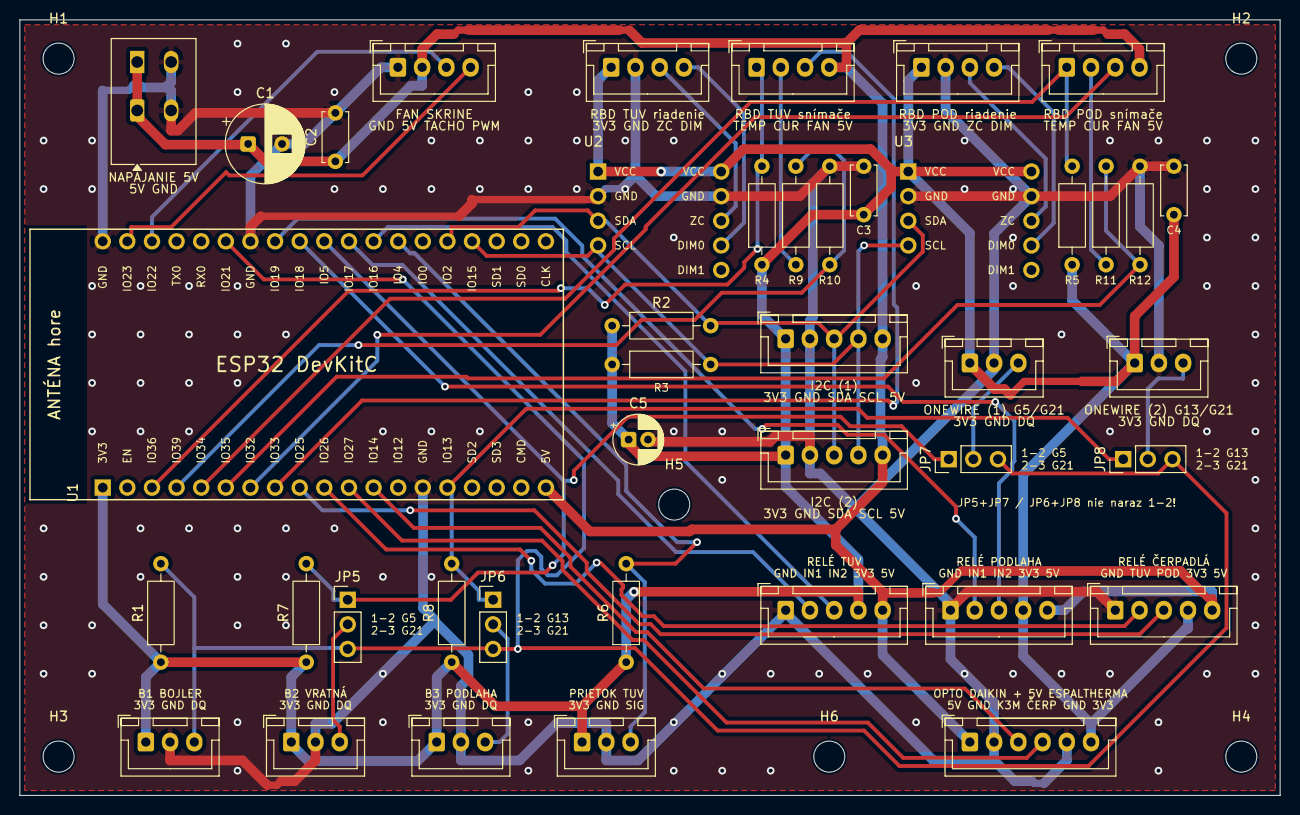
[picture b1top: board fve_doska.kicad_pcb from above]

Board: 2 copper layers, 130.0 x 80.0 mm, 48 parts (0 on the bottom side), 35 nets.

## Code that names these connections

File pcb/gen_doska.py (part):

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C.append(term("J16", ["+3V3", "GND", "OW_J16"], "ONEWIRE (1) G5/G21", FP_XH))
C.append(term("J17", ["+3V3", "GND", "OW_J17"], "ONEWIRE (2) G13/G21", FP_XH))
C.append(dict(ref="JP7", sym="JP3", val="J16: 1-2 G5 | 2-3 G21", fp=FP_JP3,
              pins={"1": "OW_G5", "2": "OW_J16", "3": "OW_BOJLER"}, popis="OneWire (1): voľný G5 / zbernica G21"))
C.append(dict(ref="JP8", sym="JP3", val="J17: 1-2 G13 | 2-3 G21", fp=FP_JP3,
              pins={"1": "OW_G13", "2": "OW_J17", "3": "OW_BOJLER"}, popis="OneWire (2): voľný G13 / zbernica G21"))
# ventilátor skrine: JST-XH 4-pin ako rbdimmery (user 2026-11-15: pôvodný konektor fanu odstrihnutý)
C.append(term("J12", ["GND", "+5V", "FAN_TACHO", "FAN_PWM"], "FAN SKRINE", FP_XH))

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

R("R1", "4k7", "+3V3", "OW_BOJLER", "pull-up DS18B20 bojler")
R("R7", "4k7", "+3V3", "OW_G5", "pull-up DS18B20 vratná (vlastný pin G5)")
R("R8", "4k7", "+3V3", "OW_G13", "pull-up DS18B20 podlaha (vlastný pin G13)")
# OneWire prepínanie (user 2026-11-15, nové snímače): prepojka 1-2 = vlastný pin (G5 / G13),
# 2-3 = spoločná zbernica G21 s B1 (pull-up len R1). Pri zmene prepnúť aj firmvér!
C.append(dict(ref="JP5", sym="JP3", val="B2: 1-2 G5 | 2-3 G21", fp=FP_JP3,
              pins={"1": "OW_G5", "2": "OW_VRATNA", "3": "OW_BOJLER"}, popis="DS18B20 B2 vratná: vlastný pin / zbernica"))
C.append(dict(ref="JP6", sym="JP3", val="B3: 1-2 G13 | 2-3 G21", fp=FP_JP3,
              pins={"1": "OW_G13", "2": "OW_PODLAHA", "3": "OW_BOJLER"}, popis="DS18B20 B3 podlaha: vlastný pin / zbernica"))
R("R6", "4k7", "+3V3", "PRIETOK", "pull-up prietokomer")
R("R2", "4k7", "+3V3", "SDA", "pull-up I2C SDA")
R("R3", "4k7", "+3V3", "SCL", "pull-up I2C SCL")
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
